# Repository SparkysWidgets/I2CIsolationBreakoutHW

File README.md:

Welcome To: I2C Isolation Breakout Hardware Repo!!
================================

##### Note: This is for the I2C Isolation Breakout Hardware Version 1 Branch

I2CisoBreakout Hardware Design Files in EAGLE. Not much to say, there are some custom parts will add Library after I clean it up!

Schematic Info
-------------------------
##### Basic schematic is split into sections

- Primary and Secondary sides for (both)
- ADUM6010 Isolated DC-DC converter with on chip transformers
- ADUM1251 I2C Isolation IC, bi-directional even on SCL
- Selectable voltage output (3.3 or 5v)
- Enable/Disable selector with tri state to allow external device to control

Board Layout Info
-------------------------
##### Form Factor based on Dangerous Prototypes SoB 50mmx50mm PCB size

- Standard 2.54mm pitch header and Grove style connector
- Power on bottom with isolation IC on top, Single supply
- Power IC can be switched on or off to all for isolation with separate supplies
- Selectable voltage output (3.3 or 5v)
- Enable/Disable selector with tri state to allow external device to control

Errata
-------------------------

##### Just a quick list of current issues
- Spacing between Primary and Isolation headers needs to be shrunk to better fit a bread board
- Clear silkscreen for power selection, and voltage selection on outputs

Firmware
-------------------------

- This is a "dumb" module and doesn't need any special firmware, In fact its a direct drop in series placement for I2C devices!!

Basic Usage
-------------------------

Usages of this device is very simple, it always for direct placement in series with an existing I2C Device, For those on the Grove style connector eco-system this breakout is extremely easy to use!

####Some of the commands are:
- Galvanic Isolation of I2C sensors
- Selectable Level shifter
- Allow for Hot/Swap or power down of I2C peripherals
- Power pullups (on host mainly) separately from VCC

License Info
-------------------------

<p>This is a fully open source project released under the CC BY license</p>
<br />
<span xmlns:dct="http://purl.org/dc/terms/" property="dct:title">I2C Isolation Breakout</span> by <a xmlns:cc="http://creativecommons.org/ns#" href="www.sparkyswidgets.com" property="cc:attributionName" rel="cc:attributionURL">Ryan Edwards, Sparky's Widgets</a> is licensed under a <a rel="license" href="http://creativecommons.org/licenses/by-sa/3.0/deed.en_US">Creative Commons Attribution-ShareAlike 3.0 Unported License</a>.<br />
Based on a work at <a xmlns:dct="http://purl.org/dc/terms/" href="/portfolio-item/i2c-isolation-breakout/" rel="dct:source">http://www.sparkyswidgets.com/portfolio-item/i2c-isolation-breakout/</a>

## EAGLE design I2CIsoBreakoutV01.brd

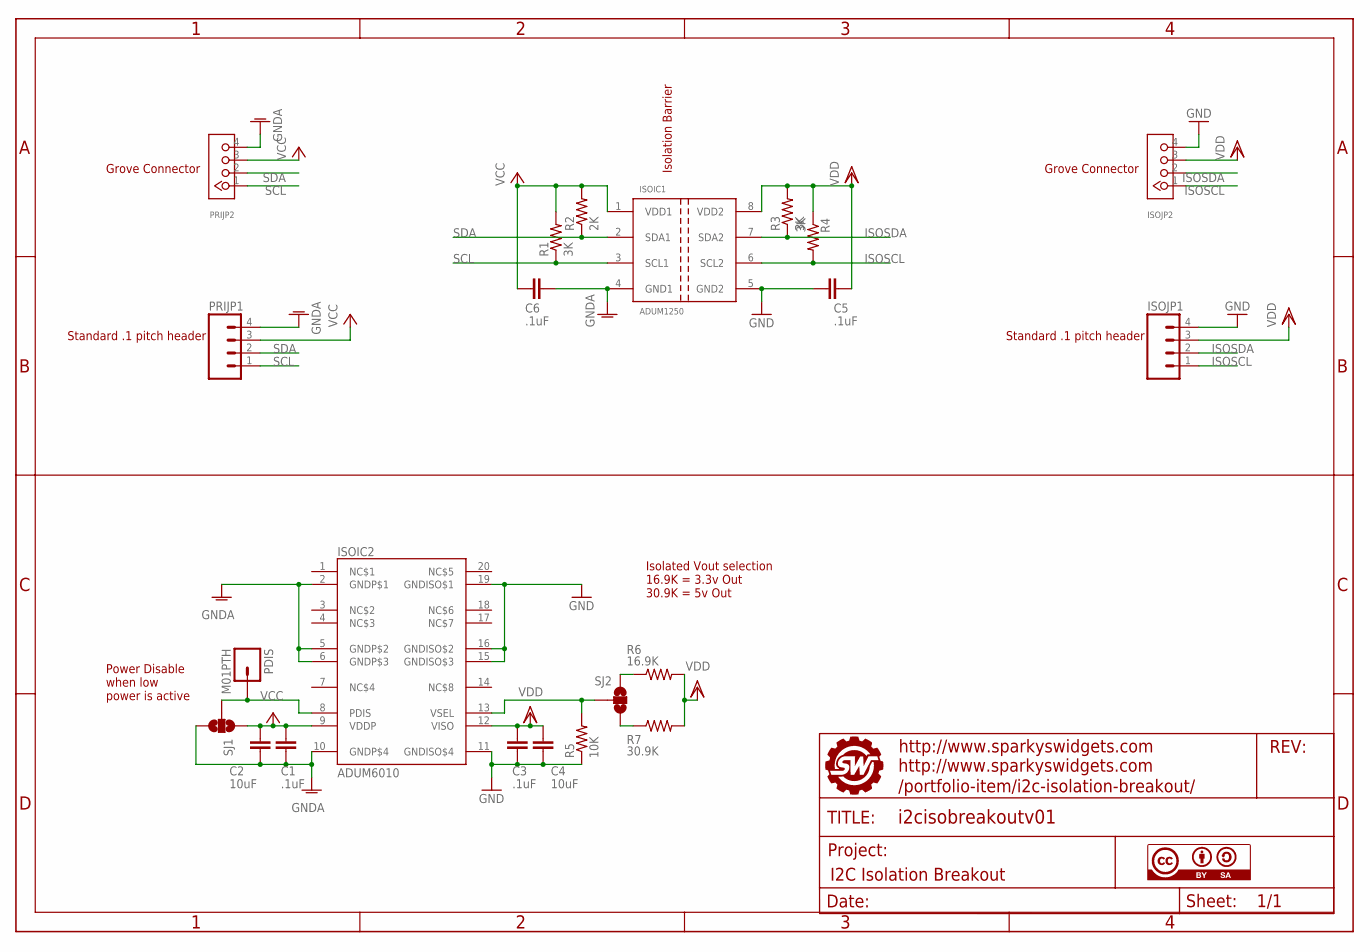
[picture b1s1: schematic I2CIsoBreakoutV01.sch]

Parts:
C1, C3, C5, C6: .1uF; 0805
C2, C4: 10uF; 0805
ISOIC1: ADUM1250; SO08
ISOIC2: ADUM6010; SSOP20
ISOJP1: M04PTH; 1X04
ISOJP2: TWIG-4P-2.0-2.0; 4P-2.0
PDIS: M01PTH; 1X01
PRIJP1: M04PTH; 1X04
PRIJP2: TWIG-4P-2.0-2.0; 4P-2.0
R1, R3, R4: 3K; 0805
R2: 2K; 0805
R5: 10K; 0805
R6: 16.9K; 0805
R7: 30.9K; 0805
SJ1, SJ2: SOLDERJUMPER_2WAYPASTE2&3; SJ_3_PASTE2&3
U$1: FRAME_ISOI2CBREAKOUT; SWPCBLOGOWITHINFO
U$2: CC-BY-SA

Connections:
GND: C3.2, C4.2, C5.1, ISOIC1.5 (GND2), ISOIC2.11 (GNDISO$4), ISOIC2.15 (GNDISO$3), ISOIC2.16 (GNDISO$2), ISOIC2.19 (GNDISO$1), ISOJP1.4, ISOJP2.4, R5.1
GNDA: C1.2, C2.2, C6.1, ISOIC1.4 (GND1), ISOIC2.2 (GNDP$1), ISOIC2.5 (GNDP$2), ISOIC2.6 (GNDP$3), ISOIC2.10 (GNDP$4), PRIJP1.4, PRIJP2.4, SJ1.3
ISOSCL: ISOIC1.6 (SCL2), ISOJP1.1, ISOJP2.1, R4.2
ISOSDA: ISOIC1.7 (SDA2), ISOJP1.2, ISOJP2.2, R3.1
unnamed: ISOIC2.8 (PDIS), PDIS.1, SJ1.2
unnamed: ISOIC2.13 (VSEL), R5.2, SJ2.2
unnamed: R6.1, SJ2.1
unnamed: R7.1, SJ2.3
SCL: ISOIC1.3 (SCL1), PRIJP1.1, PRIJP2.1, R1.1
SDA: ISOIC1.2 (SDA1), PRIJP1.2, PRIJP2.2, R2.1
VCC: C1.1, C2.1, C6.2, ISOIC1.1 (VDD1), ISOIC2.9 (VDDP), PRIJP1.3, PRIJP2.3, R1.2, R2.2, SJ1.1
VDD: C3.1, C4.1, C5.2, ISOIC1.8 (VDD2), ISOIC2.12 (VISO), ISOJP1.3, ISOJP2.3, R3.2, R4.1, R6.2, R7.2

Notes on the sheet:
Grove Connector
Standard .1 pitch header
Isolation Barrier
Power Disable when low power is active
Isolated Vout selection 16.9K = 3.3v Out 30.9K = 5v Out

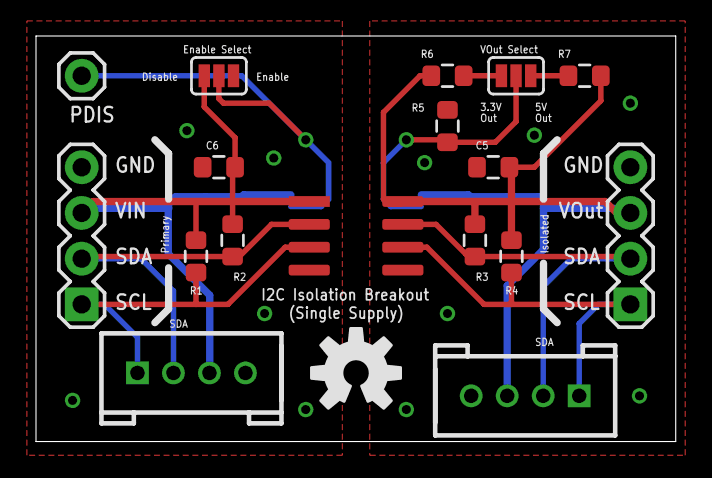
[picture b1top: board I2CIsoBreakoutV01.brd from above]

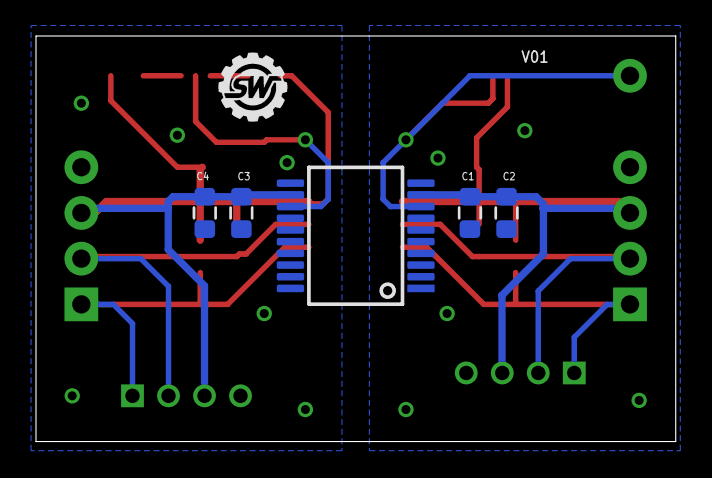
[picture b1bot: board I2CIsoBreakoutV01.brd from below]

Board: 2 copper layers, 35.5 x 22.5 mm, 25 parts (6 on the bottom side), 12 nets.

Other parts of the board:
U$3: OSHW-LOGO-M

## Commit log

2013-09-09 initial repo creation with readme
2013-09-09 Initial revision of hardware files (tested)
